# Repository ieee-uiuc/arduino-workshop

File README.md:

# arduino-workshop

The home of the IEEE@UIUC Arduino Workshop! You can find each shield and example code in the appropriate directory.

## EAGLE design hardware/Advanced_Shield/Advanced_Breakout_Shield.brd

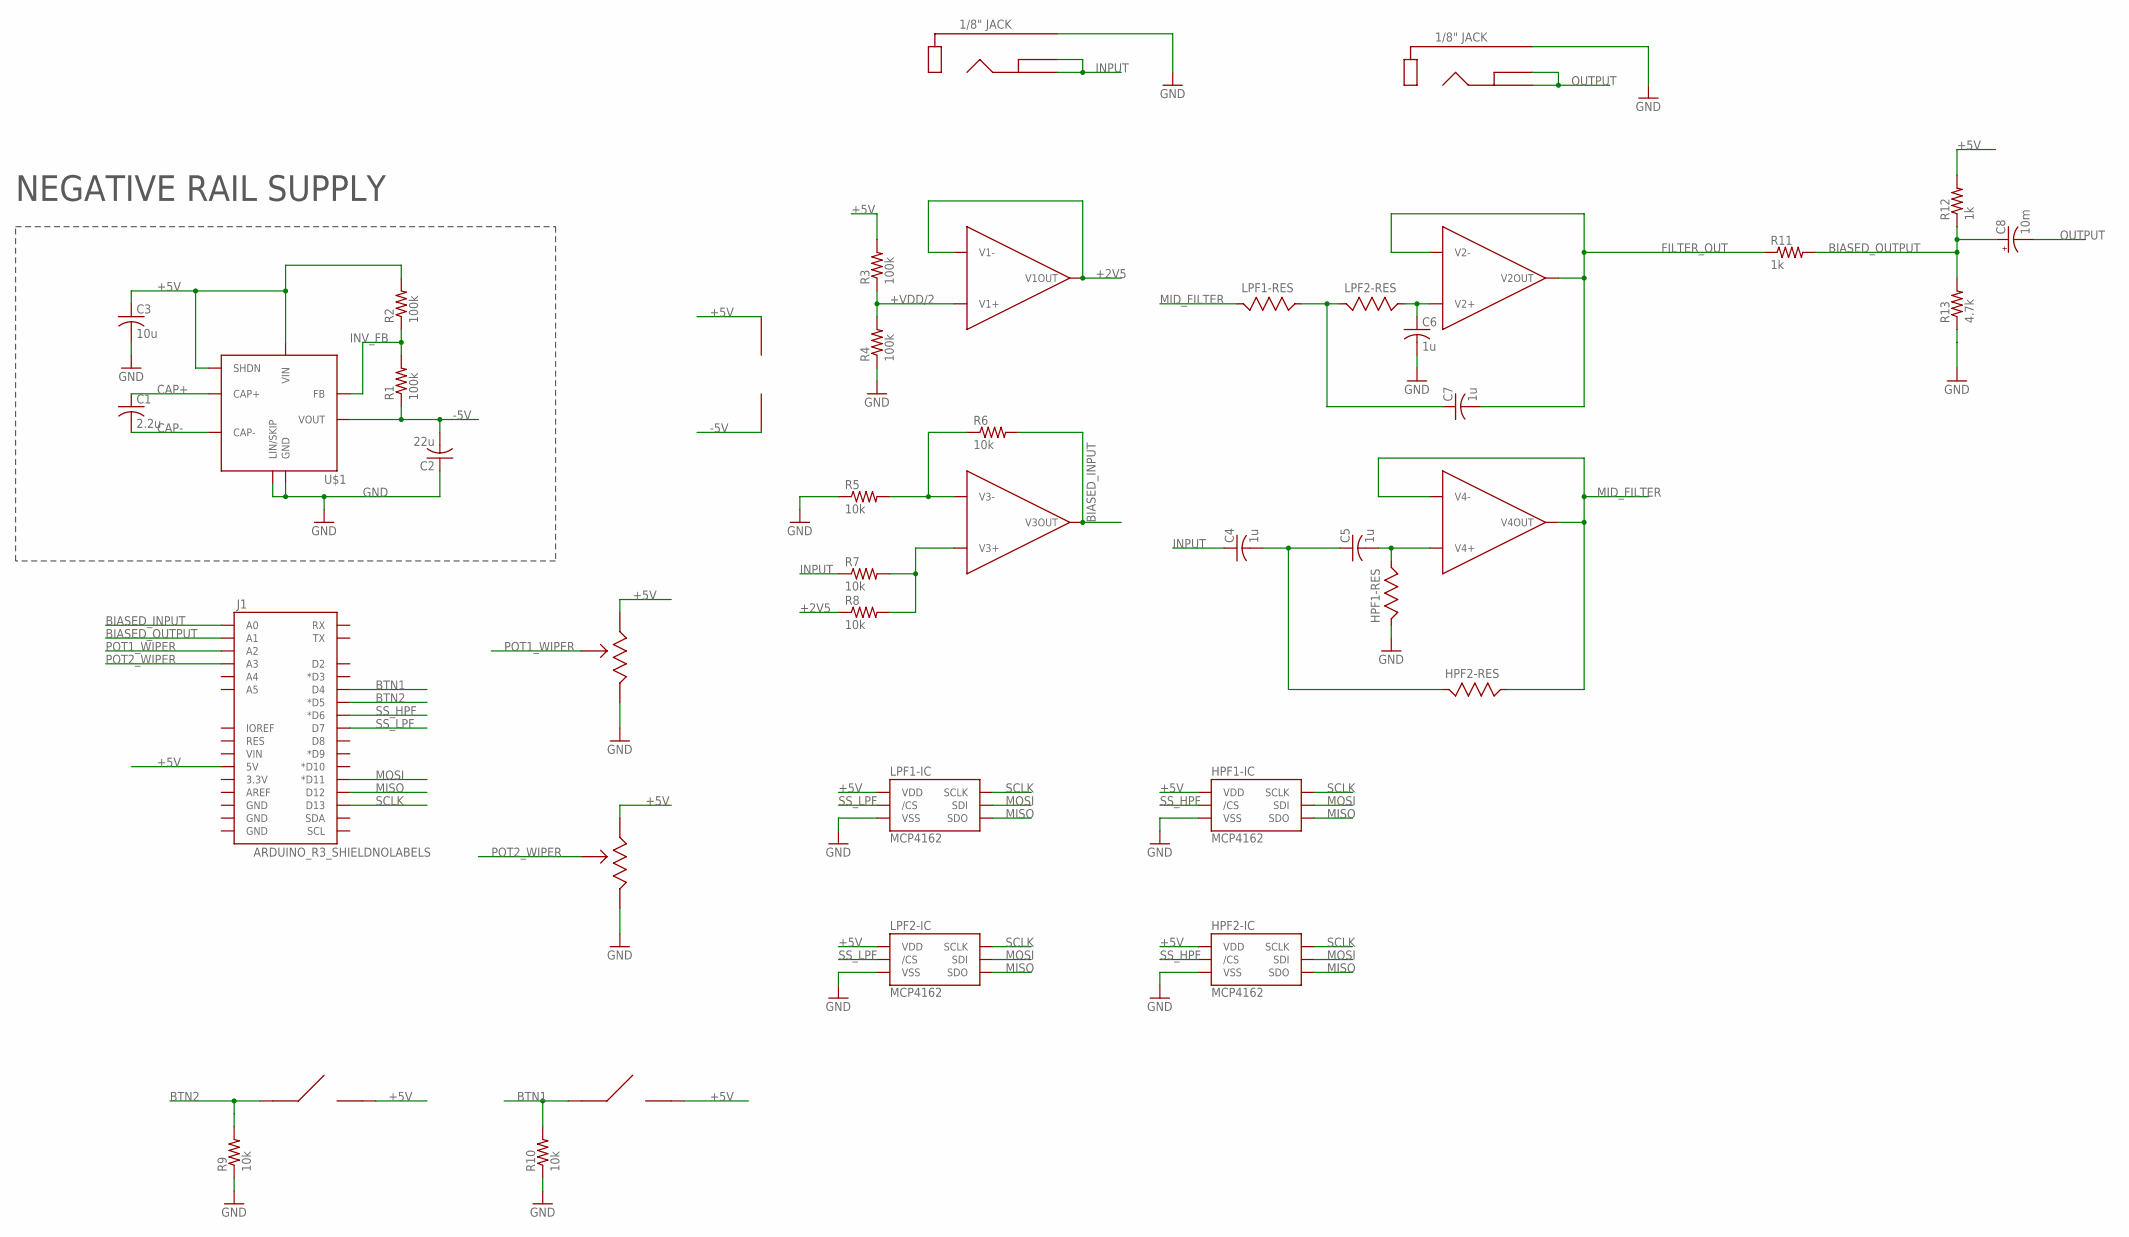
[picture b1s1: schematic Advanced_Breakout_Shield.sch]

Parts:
C1: 2.2u; C1206K
C2: 22u; C1206K
C3: 10u; C1206K
C4, C5, C6, C7: 1u; C1206K
C8: 10m; E7,5-16
HPF1, HPF2: MCP4162-502E; DIL08
J1: ARDUINO_R3_SHIELDNOLABELS; UNO_R3_SHIELD_NOLABELS
LPF1, LPF2: MCP4162-502E; DIL08
R1, R2, R3, R4: 100k; R1210
R5, R6, R7, R8, R9, R10: 10k; R1210
R11, R12: 1k; R1210
R13: 4.7k; R1210
U$1: MAX1673; SO08
U$2: TLV974; DIL14
U$3, U$4: P120PK
U$5, U$6: AUDIO_JACK
U$7, U$8: IEEE_LOGO_BUTTON

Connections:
+2V5: R8.1, U$2.1 (V1OUT), U$2.2 (V1-)
+5V: C3.1, HPF1.8 (VDD), HPF2.8 (VDD), J1.5V, LPF1.8 (VDD), LPF2.8 (VDD), R2.2, R3.2, R12.2, U$1.4 (SHDN), U$1.8 (VIN), U$2.4 (+VCC), U$3.PR (RA), U$4.PR (RA), U$7.P$2, U$8.P$2
+VDD/2: R3.1, R4.2, U$2.3 (V1+)
-5V: C2.2, R1.1, U$1.5 (VOUT), U$2.11 (-VCC)
BIASED_INPUT: J1.A0, R6.2, U$2.8 (V3OUT)
BIASED_OUTPUT: C8.+, J1.A1, R11.2, R12.1, R13.2
BTN1: J1.D4, R10.2, U$8.P$1
BTN2: J1.D5 (*D5), R9.2, U$7.P$1
CAP+: C1.1, U$1.2 (CAP+)
CAP-: C1.2, U$1.3 (CAP-)
FILTER_OUT: C7.2, R11.1, U$2.6 (V2-), U$2.7 (V2OUT)
GND: C2.1, C3.2, C6.2, HPF1.4 (VSS), HPF1.6 (BASE), HPF2.4 (VSS), LPF1.4 (VSS), LPF2.4 (VSS), R4.1, R5.1, R9.1, R10.1, R13.1, U$1.1 (LIN/SKIP), U$1.7 (GND), U$3.PM (RB), U$4.PM (RB), U$5.SLEEVE, U$6.SLEEVE
INPUT: C4.1, R7.1, U$5.RING, U$5.TIP
INV_FB: R1.2, R2.1, U$1.6 (FB)
MID_FILTER: HPF2.5 (WIPER), LPF1.6 (BASE), U$2.13 (V4-), U$2.14 (V4OUT)
MISO: HPF1.7 (SDO), HPF2.7 (SDO), J1.D12, LPF1.7 (SDO), LPF2.7 (SDO)
MOSI: HPF1.3 (SDI), HPF2.3 (SDI), J1.D11 (*D11), LPF1.3 (SDI), LPF2.3 (SDI)
unnamed: R5.2, R6.1, U$2.9 (V3-)
unnamed: C5.2, HPF1.5 (WIPER), U$2.12 (V4+)
unnamed: R7.2, R8.2, U$2.10 (V3+)
unnamed: C4.2, C5.1, HPF2.6 (BASE)
unnamed: C6.1, LPF2.5 (WIPER), U$2.5 (V2+)
unnamed: C7.1, LPF1.5 (WIPER), LPF2.6 (BASE)
OUTPUT: C8.-, U$6.RING, U$6.TIP
POT1_WIPER: J1.A2, U$3.PL (RW)
POT2_WIPER: J1.A3, U$4.PL (RW)
SCLK: HPF1.2 (SCLK), HPF2.2 (SCLK), J1.D13, LPF1.2 (SCLK), LPF2.2 (SCLK)
SS_HPF: HPF1.1 (/CS), HPF2.1 (/CS), J1.D6 (*D6)
SS_LPF: J1.D7, LPF1.1 (/CS), LPF2.1 (/CS)

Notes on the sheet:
NEGATIVE RAIL SUPPLY

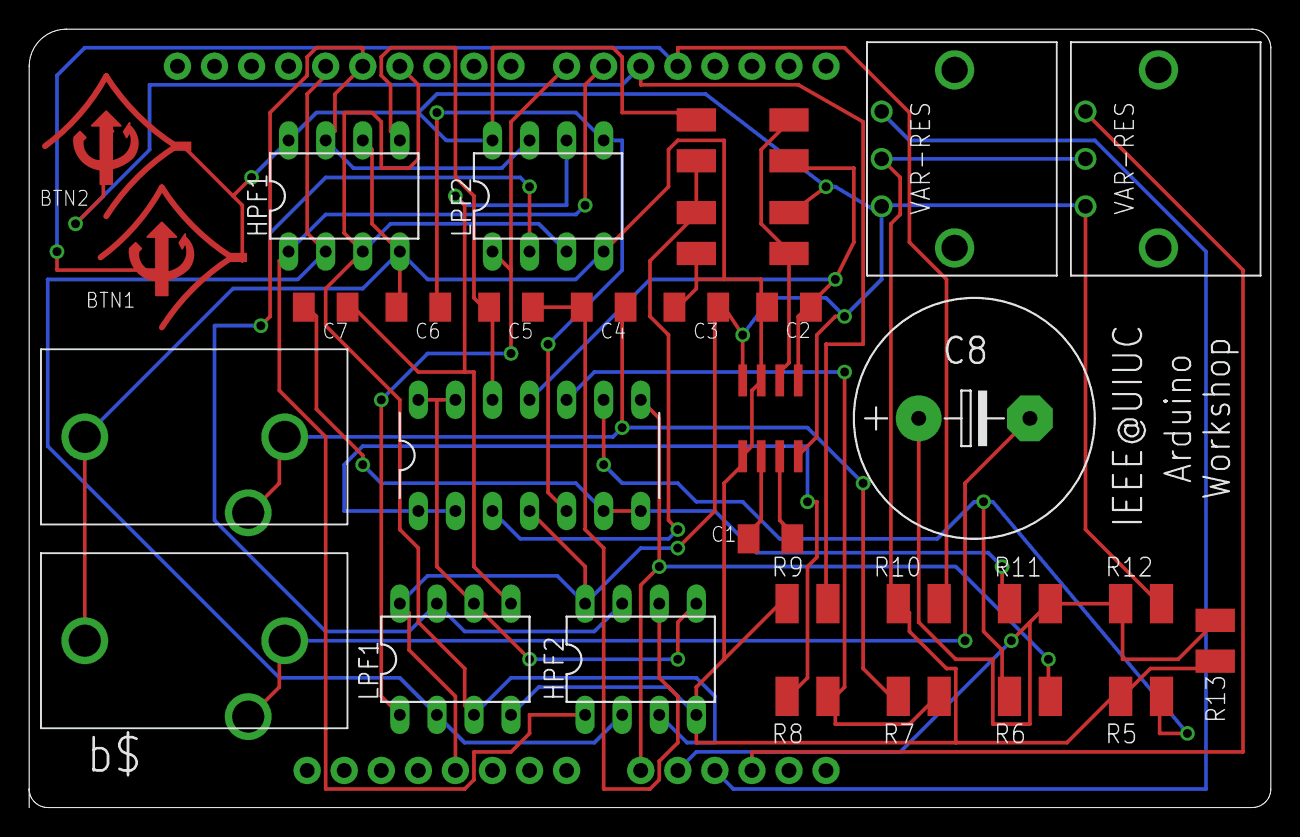
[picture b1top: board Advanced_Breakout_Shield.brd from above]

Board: 2 copper layers, 85.1 x 53.3 mm, 34 parts (0 on the bottom side), 29 nets.

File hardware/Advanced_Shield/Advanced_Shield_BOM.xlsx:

Schematic Name | Manufacturer PN | Supplier | Vendor PN | Quantity/Brd | Net Quantity | Price | Net Cost | Purpose | URL
1uF | CL31F104MBCNNNC | Digikey | 1276-2854-1-ND | 4 | 132 | 1.9300000000000001E-2 | 2.5476000000000001 | SK Filter | http://www.digikey.com/product-detail/en/CL31F104MBCNNNC/127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
10mF Cap | UVR0J103MHD | Digikey | 493-1012-ND | 1 | 33 | 0.68400000000000005 | 22.572000000000003 | AC Couple Output | http://www.digikey.com/product-detail/en/UVR0J103MHD/493-101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
10k Analog Pot | P120PK-F17BR5K | Digikey | 987-1294-ND | 2 | 66 | 0.432 | 28.512 | Manual Tuning | http://www.digikey.com/product-detail/en/P120PK-F17BR5K/987-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
1/8" Jack | MJ-3536NG | Digikey | CP-3536NG-ND | 2 | 66 | 0.85 | 56.1 | Audio In/Out | http://www.digikey.com/product-detail/en/MJ-3536NG/CP-3536NG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
10k Digital Resistor | MCP4162-502E/P | Digikey | MCP4162-502E/P-ND | 4 | 132 | 0.73 | 96.36 | SK Filter | http://www.digikey.com/product-detail/en/MCP4162-502E%2FP/MC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
Inverter | MAX1673ESA+ | Digikey | MAX1673ESA+-ND | 1 | 33 | 3.44 | 113.52 | Negative Rail | http://www.digikey.com/product-detail/en/MAX1673ESA%2B/MAX16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
2.2uF Cap | 1206YC225KAT2A | Digikey | 478-5900-1-ND | 1 | 33 | 0.46899999999999997 | 15.476999999999999 | Negative Rail | http://www.digikey.com/product-detail/en/1206YC225KAT2A/478-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
10uF Cap | 1206YC106KAT2A | Digikey | 478-5725-1-ND | 1 | 33 | 0.79500000000000004 | 26.235000000000003 | Negative Rail | http://www.digikey.com/product-detail/en/1206YC106KAT2A/478-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
22uF Cap | 12066C226KAT2A | Digikey | 478-5997-1-ND | 1 | 33 | 1.1479999999999999 | 37.884 | Negative Rail | http://www.digikey.com/product-detail/en/12066C226KAT2A/478-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
100k Resistor | 311-100KERCT-ND | Digikey | RC1206JR-07100KL | 4 | 132 | 9.9000000000000008E-3 | 1.3068000000000002 | Negative Rail / Voltage Buffer | http://www.digikey.com/product-detail/en/RC1206JR-07100KL/31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
TLV974 | TL974IN | Digikey | 296-39237-5-ND | 1 | 33 | 0.80100000000000005 | 26.433 | Quad Op Amp | http://www.digikey.com/product-detail/en/TL974IN/296-39237-5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
10k Resistor | RC1206JR-0710KL | Digikey | 311-10KERCT-ND | 6 | 198 | 9.9000000000000008E-3 | 1.9602000000000002 | Input Bias / Button Pull Down | http://www.digikey.com/product-detail/en/RC1206JR-0710KL/311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
1k Resistor | RC1206JR-071KL | Digikey | 311-1.0KERCT-ND | 2 | 66 | 1.7600000000000001E-2 | 1.1616 | Output Bias | http://www.digikey.com/product-detail/en/RC1206JR-071KL/311-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
4.7k Resistor | RC1206JR-074K7L | Digikey | 311-4.7KERCT-ND | 1 | 33 | 1.7600000000000001E-2 | 0.58079999999999998 | Output Bias | http://www.digikey.com/product-detail/en/RC1206JR-074K7L/311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
6x1 Male Pin Header | 3-644456-6 | Mouser | 571-3-644456-6 | 1 | 33 | 0.21 | 6.93 | Headers | http://www.mouser.com/ProductDetail/TE-Connectivity/3-644456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
8x1 Male Pin Header | 3-644456-8 | Mouser | 571-3-644456-8 | 2 | 66 | 0.47099999999999997 | 31.085999999999999 | Headers | http://www.mouser.com/ProductDetail/TE-Connectivity/3-644456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
10x1 Male Pin Header | 1-640456-0 | Mouser | 571-16404560 | 1 | 33 | 0.307 | 10.131 | Headers | http://www.mouser.com/ProductDetail/TE-Connectivity-AMP/1-64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
 |  |  |  |  |  | Total | 478.79700000000003
 |  |  |  |  |  | Each | 15.959900000000001

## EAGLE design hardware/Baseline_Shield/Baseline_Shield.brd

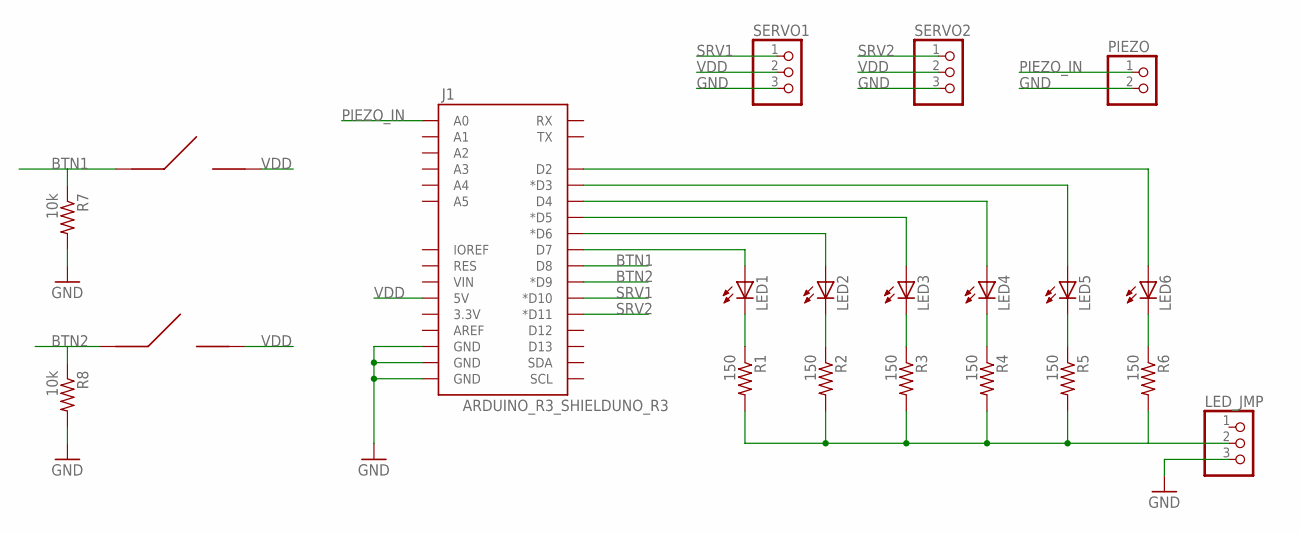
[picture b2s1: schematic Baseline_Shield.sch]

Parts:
J1: ARDUINO_R3_SHIELDUNO_R3; UNO_R3_SHIELD
LED1, LED2, LED3, LED4, LED5, LED6: LEDCHIPLED_1206; CHIPLED_1206
LED_JMP: PINHD-1X3; 1X03
PIEZO: PINHD-1X2; 1X02
R1, R2, R3, R4, R5, R6: 150; R1206
R7, R8: 10k; R1206
SERVO1, SERVO2: PINHD-1X3; 1X03
U$1, U$2: IEEE_LOGO_BUTTON

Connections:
BTN1: J1.D8, R7.1, U$2.P$1
BTN2: J1.D9 (*D9), R8.1, U$1.P$1
GND: J1.GND@0 (GND), J1.GND@1 (GND), J1.GND@2 (GND), LED_JMP.3, PIEZO.2, R7.2, R8.2, SERVO1.3, SERVO2.3
unnamed: J1.D2, LED6.A
unnamed: J1.D3 (*D3), LED5.A
unnamed: J1.D4, LED4.A
unnamed: J1.D5 (*D5), LED3.A
unnamed: J1.D6 (*D6), LED2.A
unnamed: J1.D7, LED1.A
unnamed: LED1.C, R1.1
unnamed: LED2.C, R2.1
unnamed: LED3.C, R3.1
unnamed: LED4.C, R4.1
unnamed: LED5.C, R5.1
unnamed: LED6.C, R6.1
unnamed: LED_JMP.2, R1.2, R2.2, R3.2, R4.2, R5.2, R6.2
PIEZO_IN: J1.A0, PIEZO.1
SRV1: J1.D10 (*D10), SERVO1.1
SRV2: J1.D11 (*D11), SERVO2.1
VDD: J1.5V, SERVO1.2, SERVO2.2, U$1.P$2, U$2.P$2

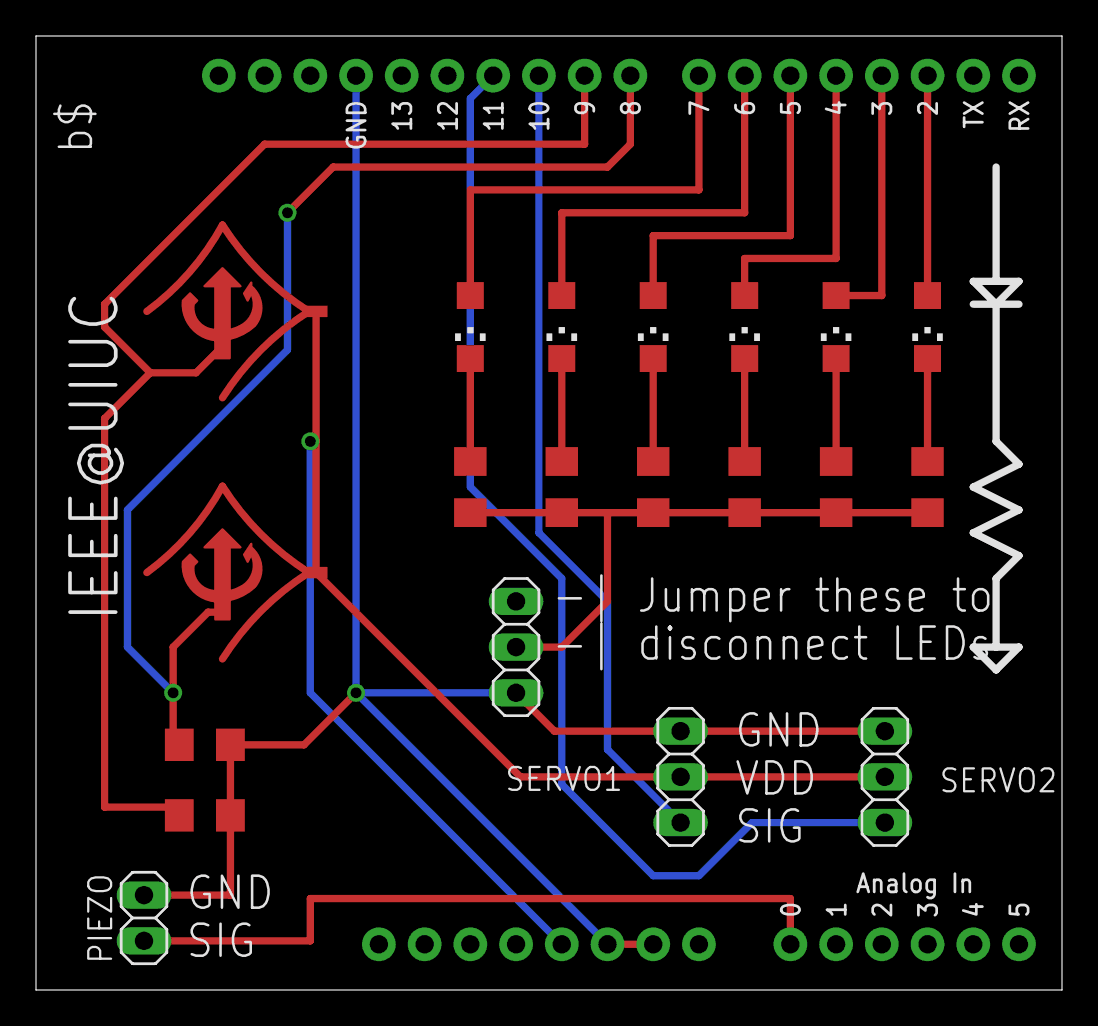
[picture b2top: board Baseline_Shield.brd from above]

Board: 2 copper layers, 57.0 x 53.0 mm, 21 parts (0 on the bottom side), 20 nets.

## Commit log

2015-10-05 init hardware
2015-10-06 bom commit
2015-10-06 updated bom
2015-10-07 make bom clearer and pushed filter code
2015-10-07 jokes next time test the code first genius
    ./ instead of /
2015-10-07 change to 6 bit
    significantly cheaper right now
2015-10-07 updating and refining hardware notes for the shields
2015-10-07 cleaning up the repo
    there's a new sheriff in town
2015-10-07 Stuff every git repo should have
2015-10-08 baseline shield eagle files
2015-10-14 filter sims
2015-10-14 advanced BOM
2015-10-14 advanced shield
2015-10-14 forgot the headers
2015-10-23 uncomplete, untested, minimal funtionality MCP4162 library
2015-10-25 Add baseline code
2015-10-25 Add blink file too for ease of access
2015-10-25 Remove placeholder
2015-10-25 Add Breakout 1 code
2015-10-25 Change code to do a full revolution on button press
2015-10-25 moved files to correct places
2015-10-25 renamed + added rework
2015-10-25 working well
    enough for government work
2015-10-25 made audio more obvious
2015-10-25 typo
2015-11-01 adding slides for breakout ii
2015-11-02 Update breakout1 code and upload example solution to LED challenge
